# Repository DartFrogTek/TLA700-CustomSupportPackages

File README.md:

# TLA700 Custom Support Packages
ISA and PCI Custom Support Packages for TLA700 with TLA software version 4.4.
- 68 Channel ISA minimal bus package. `ISA_Minimal` folder.
- 136 Channel ISA full bus package. `ISA` folder.
- 136 Channel ISA full bus package. `PCI` folder.

No real testing has been done except that each compiles with Visual Studio 6 on Windows 10 and all packages load in TLA software.

The ISA_Minimal is the only one which has been loaded onto an actual TLA7L2 module. Yet to be tested with an actual ISA bus.

## Compiling
If you fancy yourself, you can compile with Visual Studio 6.
- Double click the `ISA.dsw` workspace in the `ISA` folder.
- It will have all three DLL projects loaded. Make whichever project you want active and compile.

## Loading
- I move all files from the compiled debug folder in whichever package you've compiled.
- However you can move just the DLL file. The .tla file needs to be moved as well.
- Place folder/files on the TLA within `C:\Program Files\TLA700\Supports\PROJECTNAME`
Example: `C:\Program Files\TLA700\Supports\ISA_Minimal` contains `ISA_Minimal.dll` and `ISA_Minimal.tla`
	
You should be able to load the package onto a TLA700 module with the Load Module option.

# ISA_Mictor38 and PCI_Mictor38 Interposer boards.
- ISA and PCI interposer boards that allow the use of P3464 probes on ISA and PCI bus.
- Yet to be finalized because I need to ensure the ISA and PCI full bus packages are in working order.
- KiCAD projects.

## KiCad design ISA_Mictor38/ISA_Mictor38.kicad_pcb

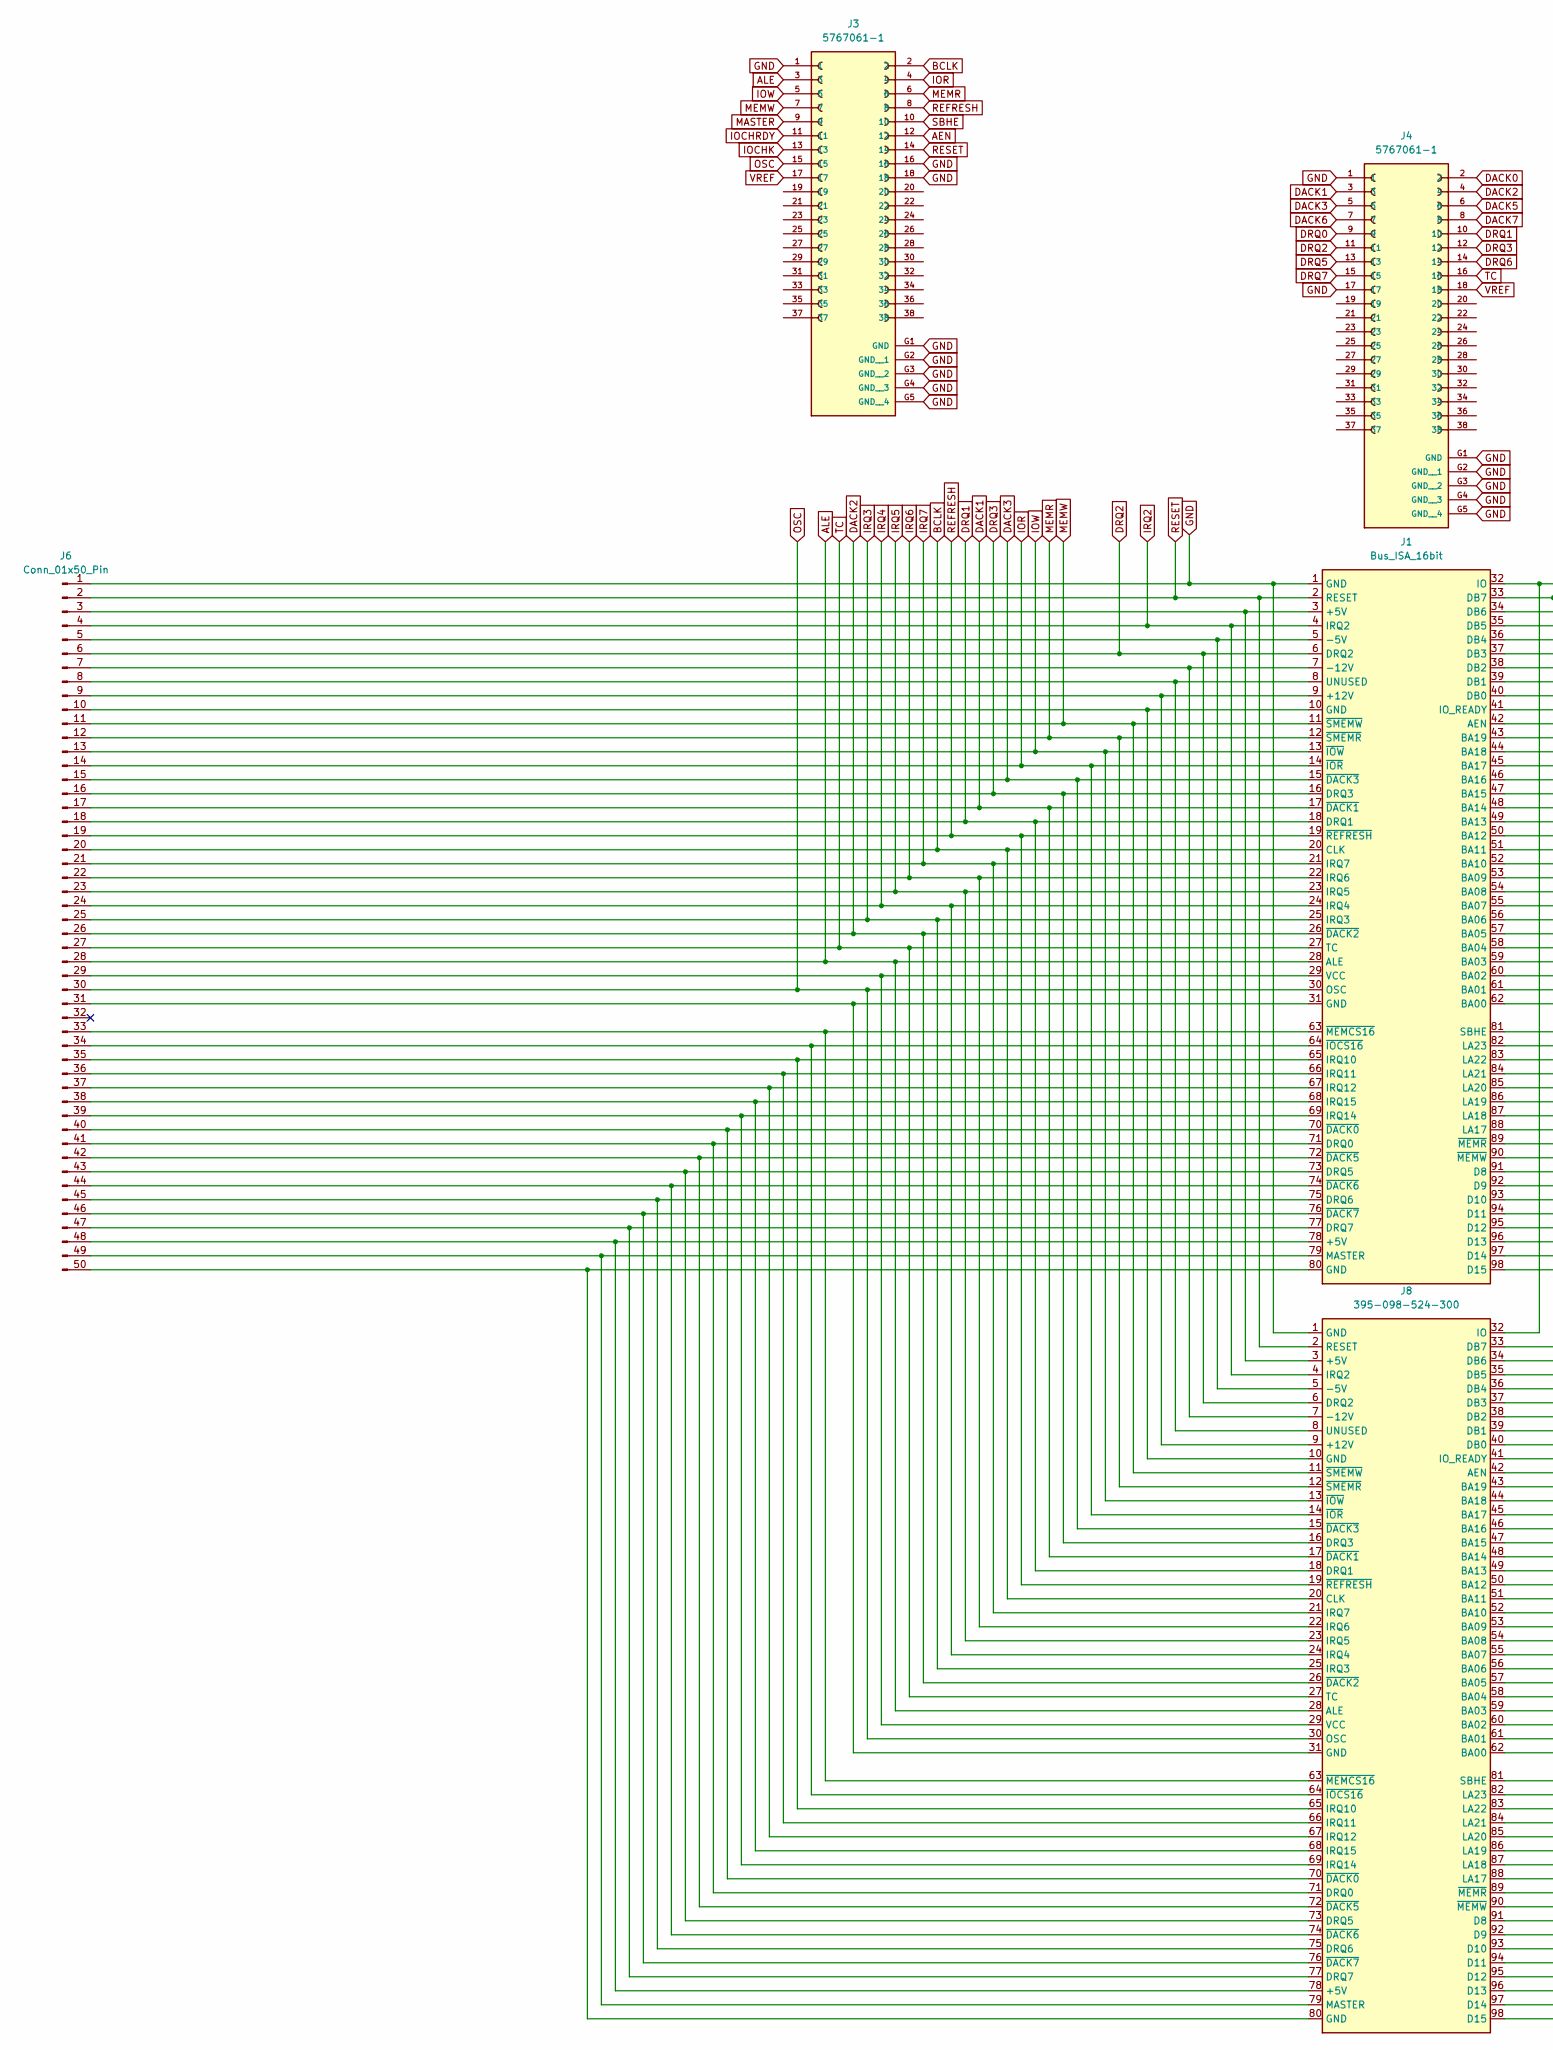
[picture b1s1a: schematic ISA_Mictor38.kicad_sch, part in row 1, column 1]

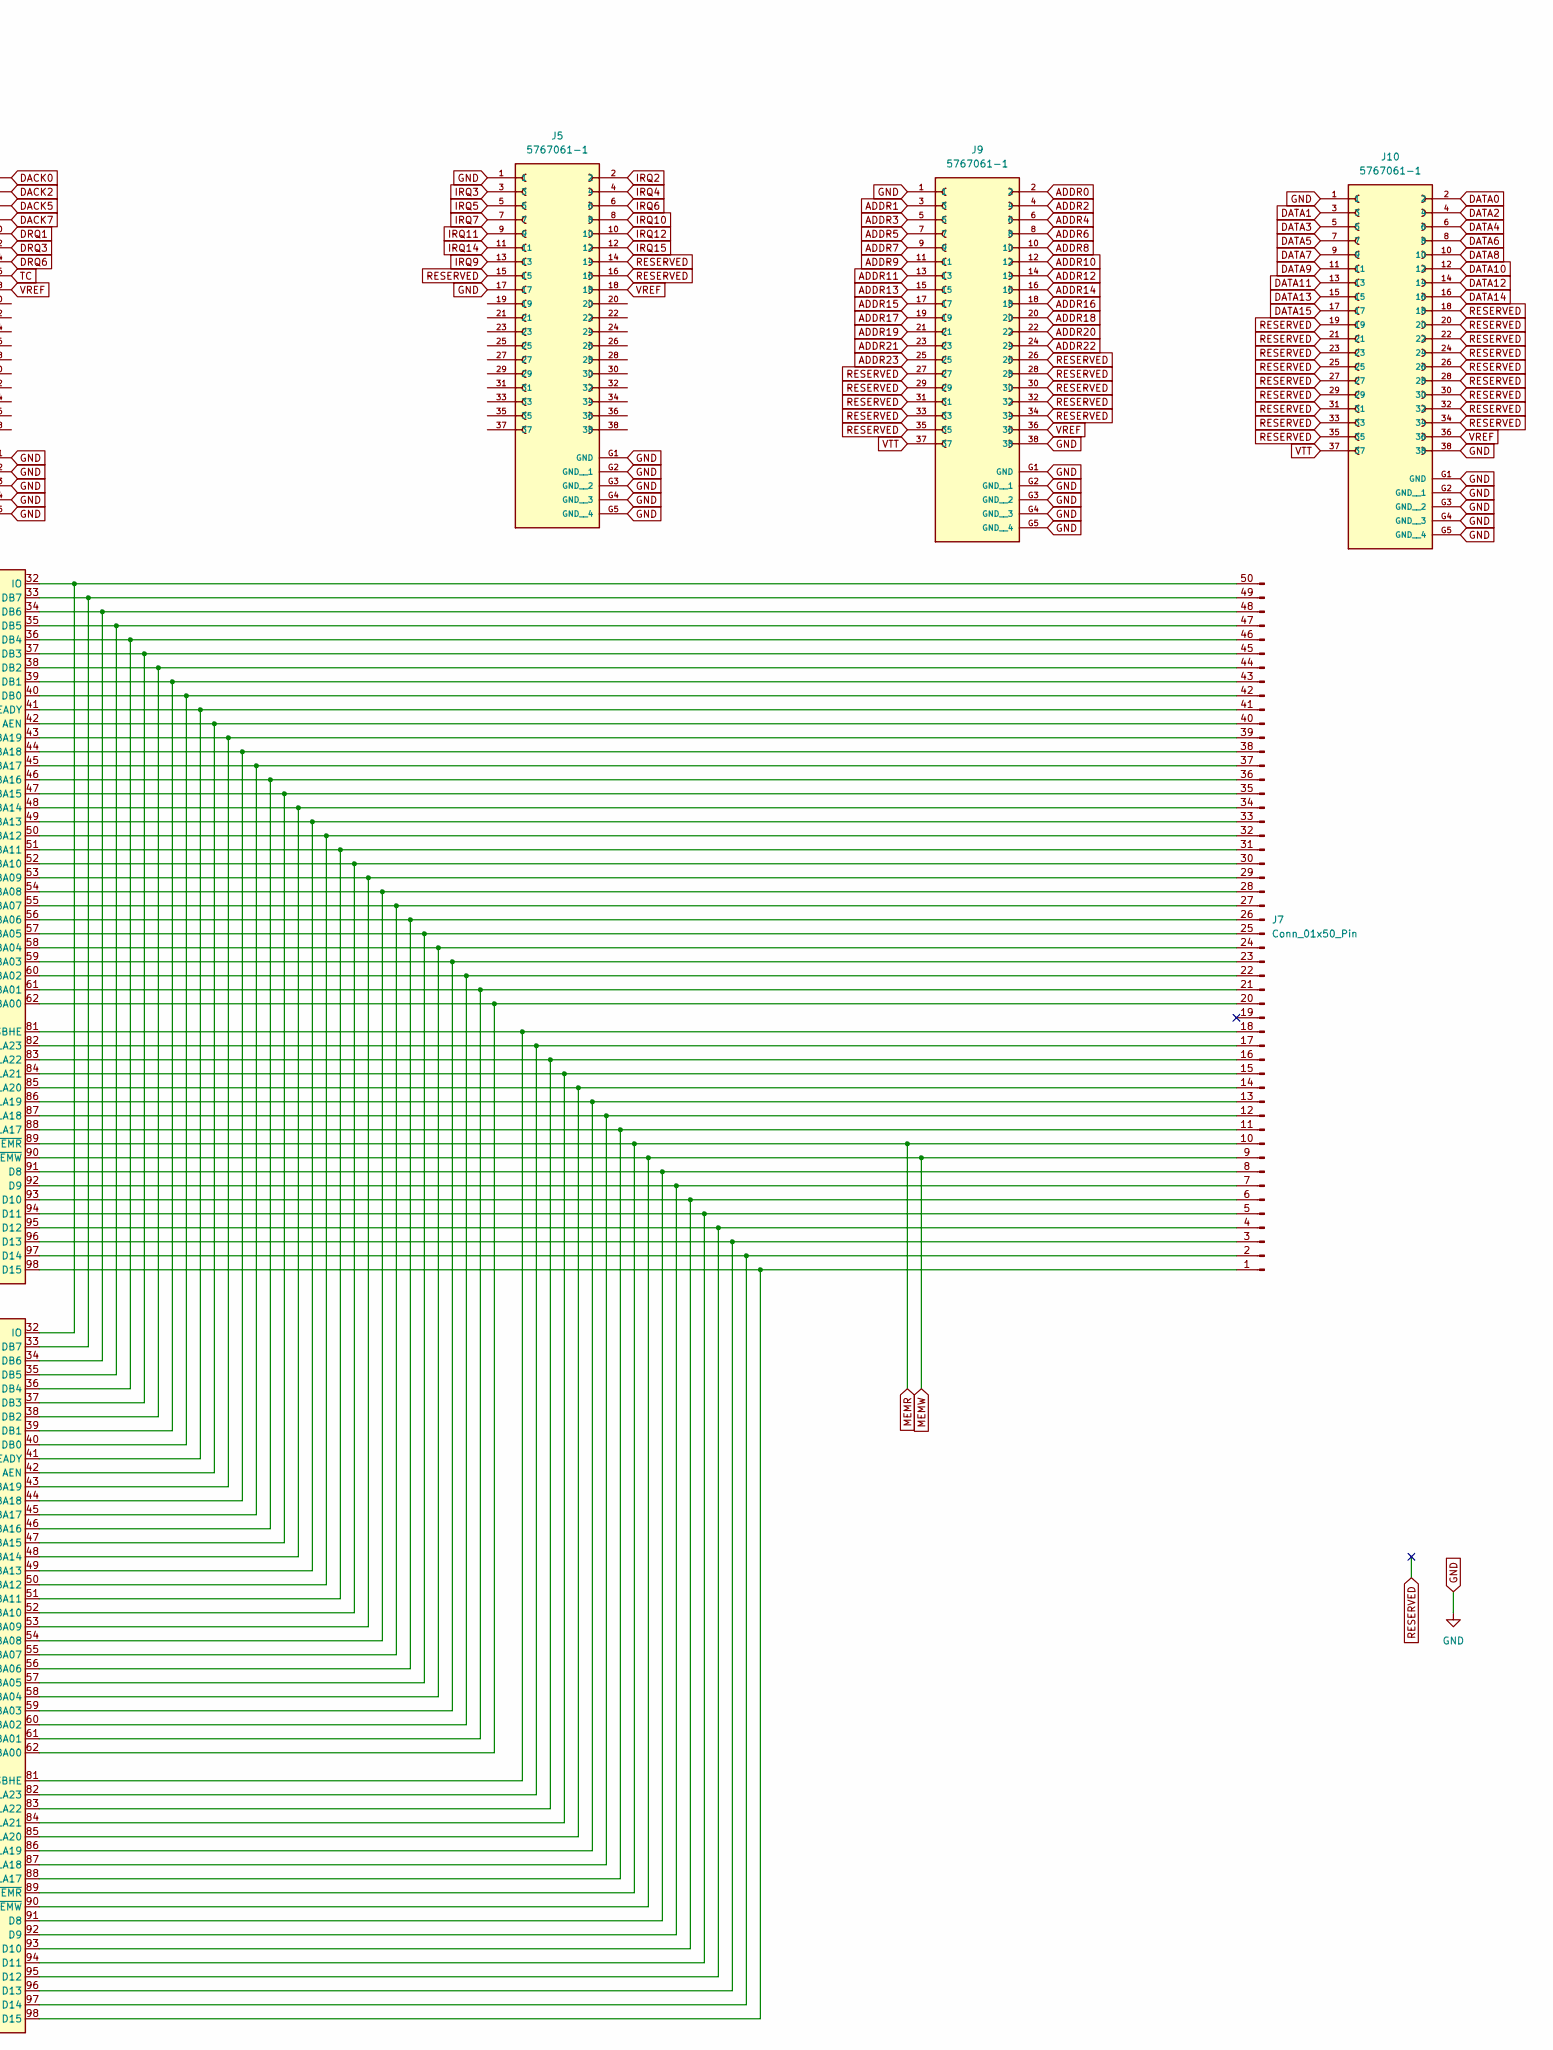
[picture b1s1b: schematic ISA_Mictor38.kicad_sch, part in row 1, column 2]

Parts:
J1: Bus_ISA_16bit; BUS_AT
J3, J4, J5, J9, J10: 5767061-1; TE_5767171-1_2x19_P0.635mm_Vertical; PARTREV B1
J6, J7: Conn_01x50_Pin; PinHeader_2x25_P2.54mm_Vertical
J8: 395-098-524-300; 395098524300; Manufacturer_Part_Number 395-098-524-300

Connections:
ADDR0: J9.2
ADDR1: J9.3
ADDR2: J9.4
ADDR3: J9.5
ADDR4: J9.6
ADDR5: J9.7
ADDR6: J9.8
ADDR7: J9.9
ADDR8: J9.10
ADDR9: J9.11
ADDR10: J9.12
ADDR11: J9.13
ADDR12: J9.14
ADDR13: J9.15
ADDR14: J9.16
ADDR15: J9.17
ADDR16: J9.18
ADDR17: J9.19
ADDR18: J9.20
ADDR19: J9.21
ADDR20: J9.22
ADDR21: J9.23
ADDR22: J9.24
ADDR23: J9.25
AEN: J3.12
ALE: J1.28 (ALE), J3.3, J6.28, J8.28 (ALE)
BCLK: J1.20 (CLK), J3.2, J6.20, J8.20 (CLK)
DACK0: J4.2
DACK1: J1.17 (~DACK1), J4.3, J6.17, J8.17 (~DACK1)
DACK2: J1.26 (~DACK2), J4.4, J6.26, J8.26 (~DACK2)
DACK3: J1.15 (~DACK3), J4.5, J6.15, J8.15 (~DACK3)
DACK5: J4.6
DACK6: J4.7
DACK7: J4.8
DATA0: J10.2
DATA1: J10.3
DATA2: J10.4
DATA3: J10.5
DATA4: J10.6
DATA5: J10.7
DATA6: J10.8
DATA7: J10.9
DATA8: J10.10
DATA9: J10.11
DATA10: J10.12
DATA11: J10.13
DATA12: J10.14
DATA13: J10.15
DATA14: J10.16
DATA15: J10.17
DRQ0: J4.9
DRQ1: J1.18 (DRQ1), J4.10, J6.18, J8.18 (DRQ1)
DRQ2: J1.6 (DRQ2), J4.11, J6.6, J8.6 (DRQ2)
DRQ3: J1.16 (DRQ3), J4.12, J6.16, J8.16 (DRQ3)
DRQ5: J4.13
DRQ6: J4.14
DRQ7: J4.15
GND: J1.1 (GND), J3.1, J3.16, J3.18, J3.G1 (GND), J3.G2 (GND__1), J3.G3 (GND__2), J3.G4 (GND__3), J3.G5 (GND__4), J4.1, J4.17, J4.G1 (GND), J4.G2 (GND__1), J4.G3 (GND__2), J4.G4 (GND__3), J4.G5 (GND__4), J5.1, J5.17, J5.G1 (GND), J5.G2 (GND__1), J5.G3 (GND__2), J5.G4 (GND__3), J5.G5 (GND__4), J6.1, J8.1 (GND), J9.1, J9.38, J9.G1 (GND), J9.G2 (GND__1), J9.G3 (GND__2), J9.G4 (GND__3), J9.G5 (GND__4), J10.1, J10.38, J10.G1 (GND), J10.G2 (GND__1), J10.G3 (GND__2), J10.G4 (GND__3), J10.G5 (GND__4)
IOCHK: J3.13
IOCHRDY: J3.11
IOR: J1.14 (~IOR), J3.4, J6.14, J8.14 (~IOR)
IOW: J1.13 (~IOW), J3.5, J6.13, J8.13 (~IOW)
IRQ2: J1.4 (IRQ2), J5.2, J6.4, J8.4 (IRQ2)
IRQ3: J1.25 (IRQ3), J5.3, J6.25, J8.25 (IRQ3)
IRQ4: J1.24 (IRQ4), J5.4, J6.24, J8.24 (IRQ4)
IRQ5: J1.23 (IRQ5), J5.5, J6.23, J8.23 (IRQ5)
IRQ6: J1.22 (IRQ6), J5.6, J6.22, J8.22 (IRQ6)
IRQ7: J1.21 (IRQ7), J5.7, J6.21, J8.21 (IRQ7)
IRQ9: J5.13
IRQ10: J5.8
IRQ11: J5.9
IRQ12: J5.10
IRQ14: J5.11
IRQ15: J5.12
MASTER: J3.9
MEMR: J1.12 (~SMEMR), J1.89 (~MEMR), J3.6, J6.12, J7.10, J8.12 (~SMEMR), J8.89 (~MEMR)
MEMW: J1.11 (~SMEMW), J1.90 (~MEMW), J3.7, J6.11, J7.9, J8.11 (~SMEMW), J8.90 (~MEMW)
unnamed: J1.9 (+12V), J6.9, J8.9 (+12V)
unnamed: J1.5 (-5V), J6.5, J8.5 (-5V)
unnamed: J1.7 (-12V), J6.7, J8.7 (-12V)
unnamed: J1.42 (AEN), J7.40, J8.42 (AEN)
unnamed: J1.62 (BA00), J7.20, J8.62 (BA00)
unnamed: J1.61 (BA01), J7.21, J8.61 (BA01)
unnamed: J1.60 (BA02), J7.22, J8.60 (BA02)
unnamed: J1.59 (BA03), J7.23, J8.59 (BA03)
unnamed: J1.58 (BA04), J7.24, J8.58 (BA04)
unnamed: J1.57 (BA05), J7.25, J8.57 (BA05)
unnamed: J1.56 (BA06), J7.26, J8.56 (BA06)
unnamed: J1.55 (BA07), J7.27, J8.55 (BA07)
unnamed: J1.54 (BA08), J7.28, J8.54 (BA08)
unnamed: J1.53 (BA09), J7.29, J8.53 (BA09)
unnamed: J1.52 (BA10), J7.30, J8.52 (BA10)
unnamed: J1.51 (BA11), J7.31, J8.51 (BA11)
unnamed: J1.50 (BA12), J7.32, J8.50 (BA12)
unnamed: J1.49 (BA13), J7.33, J8.49 (BA13)
unnamed: J1.48 (BA14), J7.34, J8.48 (BA14)
unnamed: J1.47 (BA15), J7.35, J8.47 (BA15)
unnamed: J1.46 (BA16), J7.36, J8.46 (BA16)
unnamed: J1.45 (BA17), J7.37, J8.45 (BA17)
unnamed: J1.44 (BA18), J7.38, J8.44 (BA18)
unnamed: J1.43 (BA19), J7.39, J8.43 (BA19)
unnamed: J1.91 (D8), J7.8, J8.91 (D8)
unnamed: J1.92 (D9), J7.7, J8.92 (D9)
unnamed: J1.93 (D10), J7.6, J8.93 (D10)
unnamed: J1.94 (D11), J7.5, J8.94 (D11)
unnamed: J1.95 (D12), J7.4, J8.95 (D12)
unnamed: J1.96 (D13), J7.3, J8.96 (D13)
unnamed: J1.97 (D14), J7.2, J8.97 (D14)
unnamed: J1.98 (D15), J7.1, J8.98 (D15)
unnamed: J1.40 (DB0), J7.42, J8.40 (DB0)
unnamed: J1.39 (DB1), J7.43, J8.39 (DB1)
unnamed: J1.38 (DB2), J7.44, J8.38 (DB2)
unnamed: J1.37 (DB3), J7.45, J8.37 (DB3)
unnamed: J1.36 (DB4), J7.46, J8.36 (DB4)
unnamed: J1.35 (DB5), J7.47, J8.35 (DB5)
unnamed: J1.34 (DB6), J7.48, J8.34 (DB6)
unnamed: J1.33 (DB7), J7.49, J8.33 (DB7)
unnamed: J1.71 (DRQ0), J6.41, J8.71 (DRQ0)
unnamed: J1.73 (DRQ5), J6.43, J8.73 (DRQ5)
unnamed: J1.75 (DRQ6), J6.45, J8.75 (DRQ6)
unnamed: J1.77 (DRQ7), J6.47, J8.77 (DRQ7)
unnamed: J1.32 (IO), J7.50, J8.32 (IO)
unnamed: J1.41 (IO_READY), J7.41, J8.41 (IO_READY)
unnamed: J1.65 (IRQ10), J6.35, J8.65 (IRQ10)
unnamed: J1.66 (IRQ11), J6.36, J8.66 (IRQ11)
unnamed: J1.67 (IRQ12), J6.37, J8.67 (IRQ12)
unnamed: J1.69 (IRQ14), J6.39, J8.69 (IRQ14)
unnamed: J1.68 (IRQ15), J6.38, J8.68 (IRQ15)
unnamed: J1.88 (LA17), J7.11, J8.88 (LA17)
unnamed: J1.87 (LA18), J7.12, J8.87 (LA18)
unnamed: J1.86 (LA19), J7.13, J8.86 (LA19)
unnamed: J1.85 (LA20), J7.14, J8.85 (LA20)
unnamed: J1.84 (LA21), J7.15, J8.84 (LA21)
unnamed: J1.83 (LA22), J7.16, J8.83 (LA22)
unnamed: J1.82 (LA23), J7.17, J8.82 (LA23)
unnamed: J1.79 (MASTER), J6.49, J8.79 (MASTER)
unnamed: J1.81 (SBHE), J7.18, J8.81 (SBHE)
unnamed: J1.8 (UNUSED), J6.8, J8.8 (UNUSED)
unnamed: J1.29 (VCC), J6.29, J8.29 (VCC)
unnamed: J1.70 (~DACK0), J6.40, J8.70 (~DACK0)
unnamed: J1.72 (~DACK5), J6.42, J8.72 (~DACK5)
unnamed: J1.74 (~DACK6), J6.44, J8.74 (~DACK6)
unnamed: J1.76 (~DACK7), J6.46, J8.76 (~DACK7)
unnamed: J1.64 (~IOCS16), J6.34, J8.64 (~IOCS16)
unnamed: J1.63 (~MEMCS16), J6.33, J8.63 (~MEMCS16)
unnamed: J1.3 (+5V), J6.3, J8.3 (+5V)
unnamed: J1.10 (GND), J6.10, J8.10 (GND)
unnamed: J1.31 (GND), J6.31, J8.31 (GND)
unnamed: J1.78 (+5V), J6.48, J8.78 (+5V)
unnamed: J1.80 (GND), J6.50, J8.80 (GND)
OSC: J1.30 (OSC), J3.15, J6.30, J8.30 (OSC)
REFRESH: J1.19 (~REFRESH), J3.8, J6.19, J8.19 (~REFRESH)
RESERVED: J5.14, J5.15, J5.16, J9.26, J9.27, J9.28, J9.29, J9.30, J9.31, J9.32, J9.33, J9.34, J9.35, J10.18, J10.19, J10.20, J10.21, J10.22, J10.23, J10.24, J10.25, J10.26, J10.27, J10.28, J10.29, J10.30, J10.31, J10.32, J10.33, J10.34, J10.35
RESET: J1.2 (RESET), J3.14, J6.2, J8.2 (RESET)
SBHE: J3.10
TC: J1.27 (TC), J4.16, J6.27, J8.27 (TC)
VREF: J3.17, J4.18, J5.18, J9.36, J10.36
VTT: J9.37, J10.37

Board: 2 copper layers, 9 parts (0 on the bottom side), 99 nets, no tracks yet.

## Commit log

2025-05-21 ISA/PCI custom support packages and ISA/PCI interposer boards. Proof of Concept.
